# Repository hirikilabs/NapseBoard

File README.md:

# NapseBoard

KiCAD design files for the Napse EEG Board.

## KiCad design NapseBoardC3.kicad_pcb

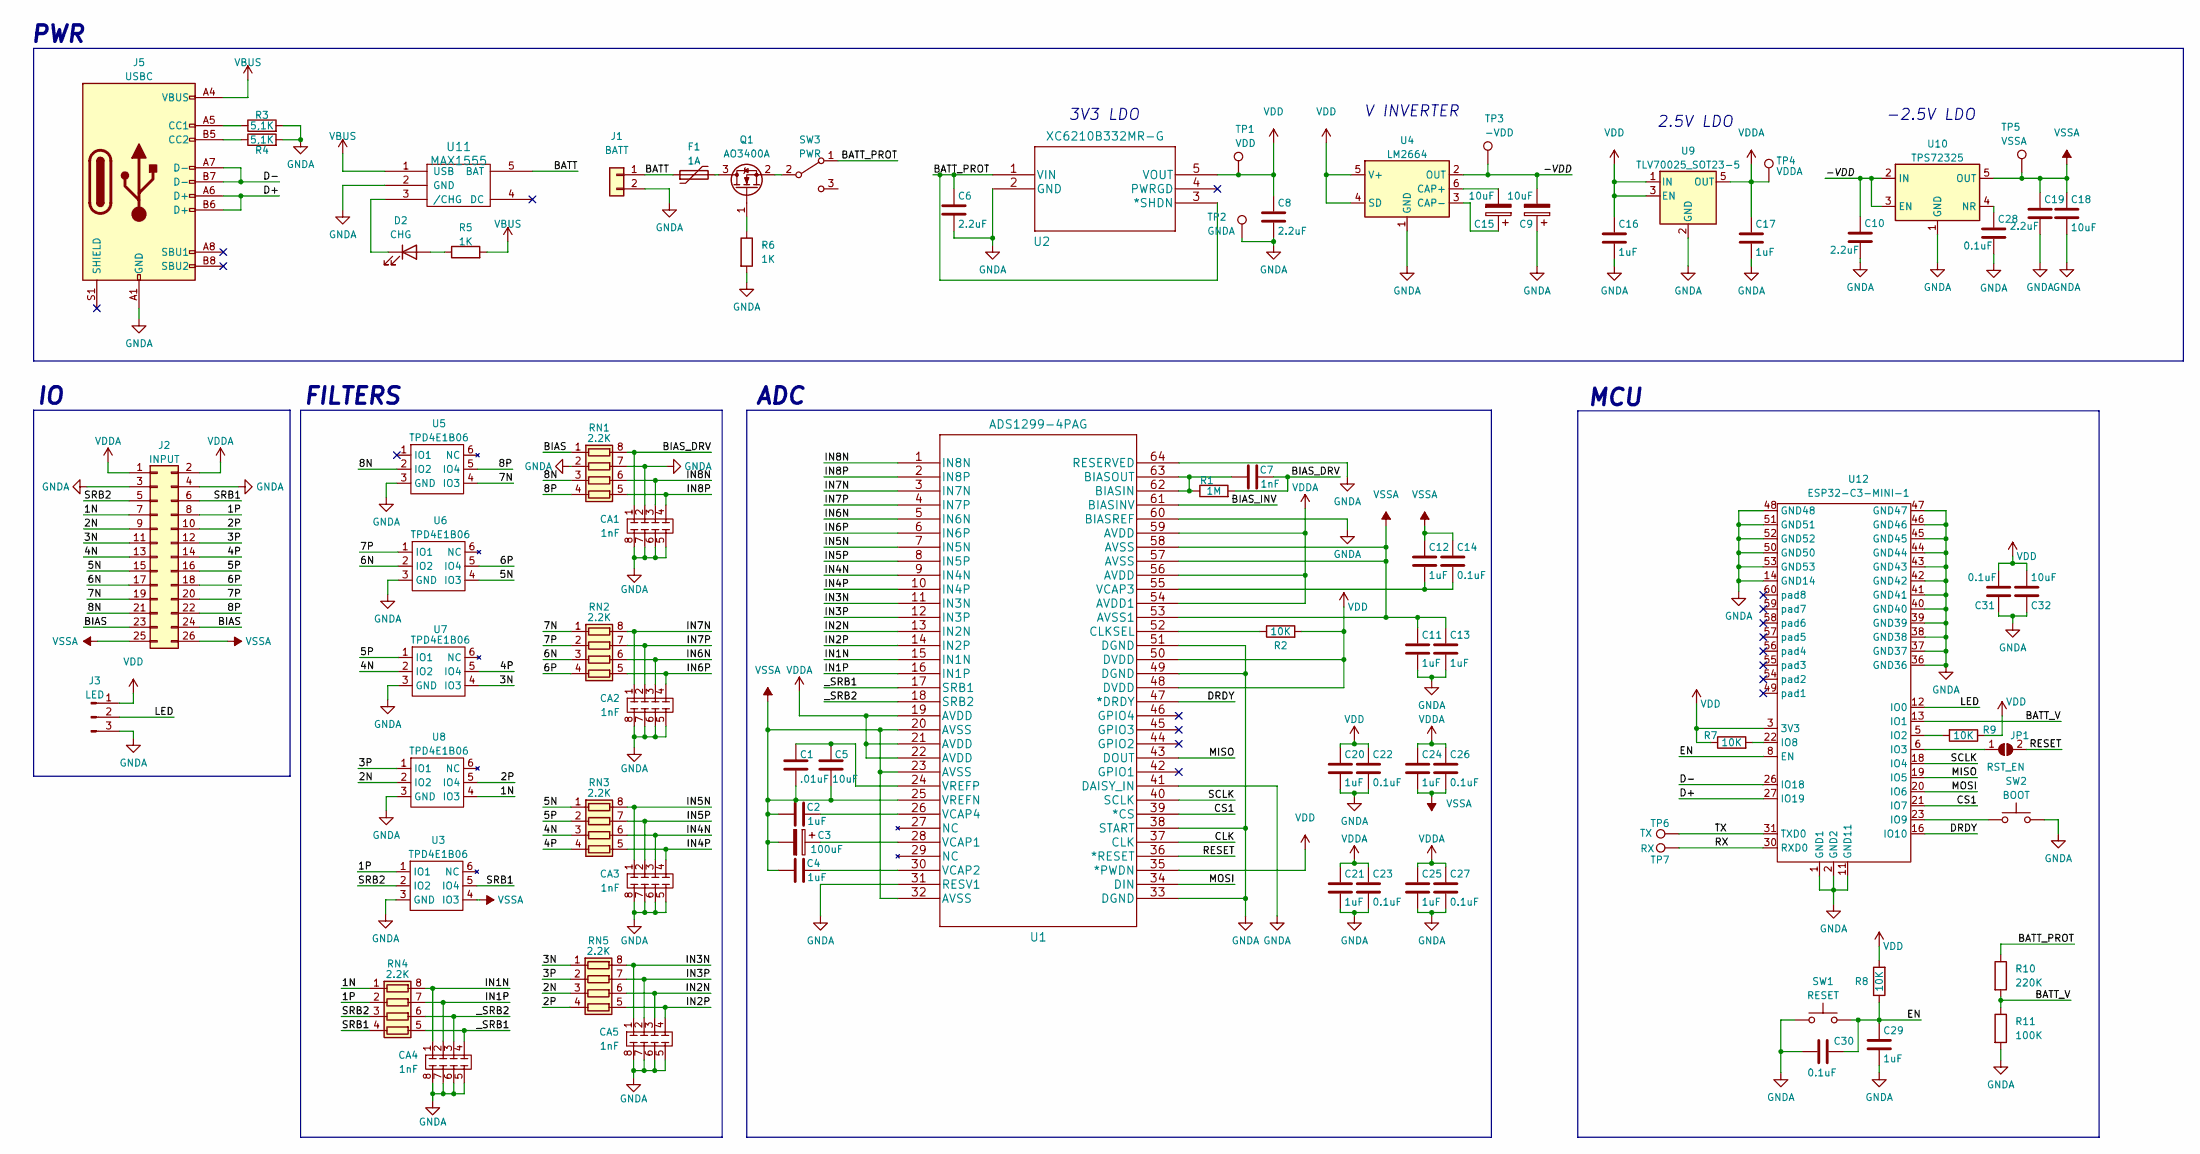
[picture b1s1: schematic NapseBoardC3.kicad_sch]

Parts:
C1: .01uF; C_0603_1608Metric
C2, C4, C11, C12, C13, C16, C17, C20, C21, C24, C25, C29: 1uF; C_0603_1608Metric
C3: 100uF; CP_EIA-3216-18_Kemet-A
C5, C9, C15, C18, C32: 10uF; C_0603_1608Metric
C6, C8, C10, C19: 2.2uF; C_0603_1608Metric
C7: 1nF; C_0603_1608Metric
C14, C22, C23, C26, C27, C28, C30, C31: 0.1uF; C_0603_1608Metric
CA1, CA2, CA3, CA4, CA5: 1nF; C_Array_4x0612
D2: CHG; LED_0603_1608Metric
F1: 1A; Fuse_1206_3216Metric
J1: BATT; PinHeader_1x02_P2.54mm_Vertical
J2: INPUT; PinHeader_2x13_P2.54mm_Horizontal
J3: LED; PinSocket_1x03_P2.00mm_Vertical
J5: USBC; USB_C_Receptacle_XKB_U262-16XN-4BVC11
JP1: RST_EN; SolderJumper-2_P1.3mm_Open_TrianglePad1.0x1.5mm
Q1: AO3400A; SOT-23
R1: 1M; R_0603_1608Metric
R2, R7, R8, R9: 10K; R_0603_1608Metric
R3, R4: 5,1K; R_0603_1608Metric
R5, R6: 1K; R_0603_1608Metric
R10: 220K; R_0603_1608Metric
R11: 100K; R_0603_1608Metric
RN1, RN2, RN3, RN4, RN5: 2.2K; R_Array_Convex_4x0603
SW1: RESET; SW_Push_SPST_NO_Alps_SKRK
SW2: BOOT; SW_Push_SPST_NO_Alps_SKRK
SW3: PWR; SW_SPDT_PCM12
TP1: VDD; TestPoint_Pad_D1.0mm
TP2: GNDA; TestPoint_Pad_D1.0mm
TP3: -VDD; TestPoint_Pad_D1.0mm
TP4: VDDA; TestPoint_Pad_D1.0mm
TP5: VSSA; TestPoint_Pad_D1.0mm
TP6: TX; TestPoint_Pad_D1.0mm
TP7: RX; TestPoint_Pad_D1.0mm
U1: ADS1299-4PAG; TQFP-64_10x10mm_P0.5mm
U2: XC6210B332MR-G; SOT-23-5
U3, U5, U6, U7, U8: TPD4E1B06; SOT-363_SC-70-6
U4: LM2664; SOT-23-6
U9: TLV70025_SOT23-5; SOT-23-5
U10: TPS72325; SOT-23-5
U11: MAX1555; SOT-23-5
U12: ESP32-C3-MINI-1

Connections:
/1N: J2.7, RN4.1 (R1.1), U8.4 (IO3)
/1P: J2.8, RN4.2 (R2.1), U3.1 (IO1)
/2N: J2.9, RN5.3 (R3.1), U8.2 (IO2)
/2P: J2.10, RN5.4 (R4.1), U8.5 (IO4)
/3N: J2.11, RN5.1 (R1.1), U7.4 (IO3)
/3P: J2.12, RN5.2 (R2.1), U8.1 (IO1)
/4N: J2.13, RN3.3 (R3.1), U7.2 (IO2)
/4P: J2.14, RN3.4 (R4.1), U7.5 (IO4)
/5N: J2.15, RN3.1 (R1.1), U6.4 (IO3)
/5P: J2.16, RN3.2 (R2.1), U7.1 (IO1)
/6N: J2.17, RN2.3 (R3.1), U6.2 (IO2)
/6P: J2.18, RN2.4 (R4.1), U6.5 (IO4)
/7N: J2.19, RN2.1 (R1.1), U5.4 (IO3)
/7P: J2.20, RN2.2 (R2.1), U6.1 (IO1)
/8N: J2.21, RN1.3 (R3.1), U5.2 (IO2)
/8P: J2.22, RN1.4 (R4.1), U5.5 (IO4)
/-VDD: C9.2, C10.1, TP3.1, U4.2 (OUT), U10.2 (IN), U10.3 (EN)
/BATT: F1.1, J1.1, U11.5 (BAT)
/BATT_PROT: C6.1, R10.1, SW3.1 (A), U2.1 (VIN), U2.3 (*SHDN)
/BATT_V: R10.2, R11.1, U12.13 (IO1)
/BIAS: J2.23, J2.24, RN1.1 (R1.1)
/BIAS_DRV: C7.2, CA1.1, R1.2, RN1.8 (R1.2)
/BIAS_INV: U1.61 (BIASINV)
/CLK: U1.37 (CLK)
/CS1: U1.39 (*CS), U12.21 (IO7)
/D+: J5.A6 (D+), J5.B6 (D+), U12.27 (IO19)
/D-: J5.A7 (D-), J5.B7 (D-), U12.26 (IO18)
/DRDY: U1.47 (*DRDY), U12.16 (IO10)
/EN: C29.1, C30.2, R8.1, SW1.2, U12.8 (EN)
/IN1N: CA4.1, RN4.8 (R1.2), U1.15 (IN1N)
/IN1P: CA4.2, RN4.7 (R2.2), U1.16 (IN1P)
/IN2N: CA5.3, RN5.6 (R3.2), U1.13 (IN2N)
/IN2P: CA5.4, RN5.5 (R4.2), U1.14 (IN2P)
/IN3N: CA5.1, RN5.8 (R1.2), U1.11 (IN3N)
/IN3P: CA5.2, RN5.7 (R2.2), U1.12 (IN3P)
/IN4N: CA3.3, RN3.6 (R3.2), U1.9 (IN4N)
/IN4P: CA3.4, RN3.5 (R4.2), U1.10 (IN4P)
/IN5N: CA3.1, RN3.8 (R1.2), U1.7 (IN5N)
/IN5P: CA3.2, RN3.7 (R2.2), U1.8 (IN5P)
/IN6N: CA2.3, RN2.6 (R3.2), U1.5 (IN6N)
/IN6P: CA2.4, RN2.5 (R4.2), U1.6 (IN6P)
/IN7N: CA2.1, RN2.8 (R1.2), U1.3 (IN7N)
/IN7P: CA2.2, RN2.7 (R2.2), U1.4 (IN7P)
/IN8N: CA1.3, RN1.6 (R3.2), U1.1 (IN8N)
/IN8P: CA1.4, RN1.5 (R4.2), U1.2 (IN8P)
/LED: J3.2, U12.12 (IO0)
/MISO: U1.43 (DOUT), U12.19 (IO5)
/MOSI: U1.34 (DIN), U12.20 (IO6)
/RESET: JP1.2 (B), U1.36 (*RESET)
/RX: TP7.1, U12.30 (RXD0)
/SCLK: U1.40 (SCLK), U12.18 (IO4)
/SRB1: J2.6, RN4.4 (R4.1), U3.5 (IO4)
/SRB2: J2.5, RN4.3 (R3.1), U3.2 (IO2)
/TX: TP6.1, U12.31 (TXD0)
/_SRB1: CA4.4, RN4.5 (R4.2), U1.17 (SRB1)
/_SRB2: CA4.3, RN4.6 (R3.2), U1.18 (SRB2)
GNDA: C6.2, C8.2, C9.1, C10.2, C11.2, C13.2, C16.2, C17.2, C18.2, C19.2, C20.2, C21.2, C22.2, C23.2, C25.2, C27.2, C28.2, C29.2, C30.1, C31.2, C32.2, CA1.2, CA1.5, CA1.6, CA1.7, CA1.8, CA2.5, CA2.6, CA2.7, CA2.8, CA3.5, CA3.6, CA3.7, CA3.8, CA4.5, CA4.6, CA4.7, CA4.8, CA5.5, CA5.6, CA5.7, CA5.8, J1.2, J2.3, J2.4, J3.3, J5.A1 (GND), J5.A12 (GND), J5.B1 (GND), J5.B12 (GND), R3.2, R4.2, R6.2, R11.2, RN1.2 (R2.1), RN1.7 (R2.2), SW1.1, SW2.2, TP2.1, U1.31 (RESV1), U1.33 (DGND), U1.38 (START), U1.41 (DAISY_IN), U1.49 (DGND), U1.51 (DGND), U1.60 (BIASREF), U1.64 (RESERVED), U2.2 (GND), U3.3 (GND), U4.1 (GND), U5.3 (GND), U6.3 (GND), U7.3 (GND), U8.3 (GND), U9.2 (GND), U10.1 (GND), U11.2 (GND), U12.1 (GND1), U12.2 (GND2), U12.11 (GND11), U12.14 (GND14), U12.36 (GND36), U12.37 (GND37), U12.38 (GND38), U12.39 (GND39), U12.40 (GND40), U12.41 (GND41), U12.42 (GND42), U12.43 (GND43), U12.44 (GND44), U12.45 (GND45), U12.46 (GND46), U12.47 (GND47), U12.48 (GND48), U12.50 (GND50), U12.51 (GND51), U12.52 (GND52), U12.53 (GND53)
unnamed: D2.2 (A), R5.1
unnamed: D2.1 (K), U11.3 (/CHG)
unnamed: J5.A5 (CC1), R3.1
unnamed: J5.B5 (CC2), R4.1
unnamed: JP1.1 (A), U12.6 (IO3)
unnamed: F1.2, Q1.3 (D)
unnamed: Q1.1 (G), R6.1
unnamed: Q1.2 (S), SW3.2 (B)
unnamed: C7.1, R1.1, U1.62 (BIASIN), U1.63 (BIASOUT)
unnamed: R2.1, U1.52 (CLKSEL)
unnamed: C3.1, U1.28 (VCAP1)
unnamed: C4.2, U1.30 (VCAP2)
unnamed: C12.2, C14.2, U1.55 (VCAP3)
unnamed: C2.2, U1.26 (VCAP4)
unnamed: C1.1, C5.2, U1.24 (VREFP)
unnamed: C15.2, U4.6 (CAP+)
unnamed: C15.1, U4.3 (CAP-)
unnamed: C28.1, U10.4 (NR)
unnamed: R9.2, U12.5 (IO2)
unnamed: R7.2, U12.22 (IO8)
unnamed: SW2.1, U12.23 (IO9)
VBUS: J5.A4 (VBUS), J5.A9 (VBUS), J5.B4 (VBUS), J5.B9 (VBUS), R5.2, U11.1 (USB)
VDD: C8.1, C16.1, C20.1, C22.1, C31.1, C32.1, J3.1, R2.2, R7.1, R8.2, R9.1, TP1.1, U1.35 (*PWDN), U1.48 (DVDD), U1.50 (DVDD), U2.5 (VOUT), U4.4 (SD), U4.5 (V+), U9.1 (IN), U9.3 (EN), U12.3 (3V3)
VDDA: C17.1, C21.1, C23.1, C24.1, C25.1, C26.1, C27.1, J2.1, J2.2, TP4.1, U1.19 (AVDD), U1.21 (AVDD), U1.22 (AVDD), U1.54 (AVDD1), U1.56 (AVDD), U1.59 (AVDD), U9.5 (OUT)
VSSA: C1.2, C2.1, C3.2, C4.1, C5.1, C11.1, C12.1, C13.1, C14.1, C18.1, C19.1, C24.2, C26.2, J2.25, J2.26, TP5.1, U1.20 (AVSS), U1.23 (AVSS), U1.25 (VREFN), U1.32 (AVSS), U1.53 (AVSS1), U1.57 (AVSS), U1.58 (AVSS), U3.4 (IO3), U10.5 (OUT)

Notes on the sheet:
2.5V LDO
V INVERTER
3V3 LDO
FILTERS
MCU
-2.5V LDO
PWR
ADC

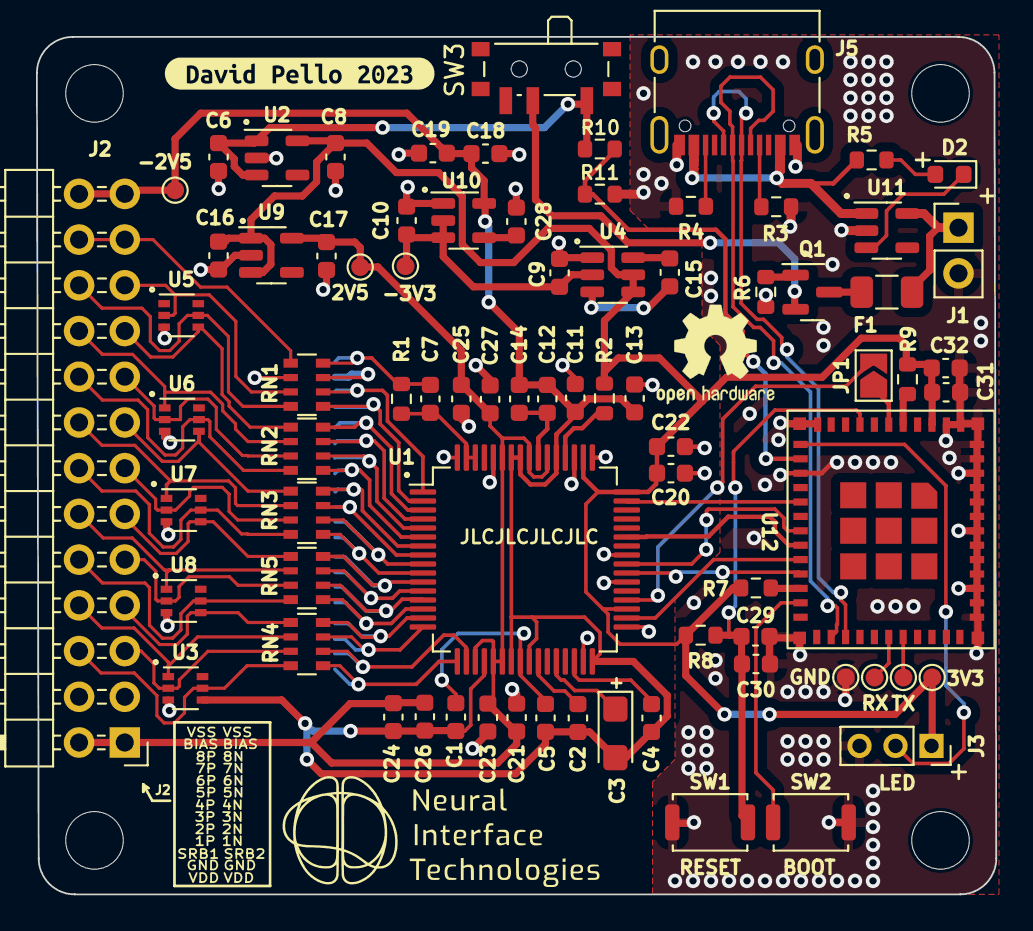
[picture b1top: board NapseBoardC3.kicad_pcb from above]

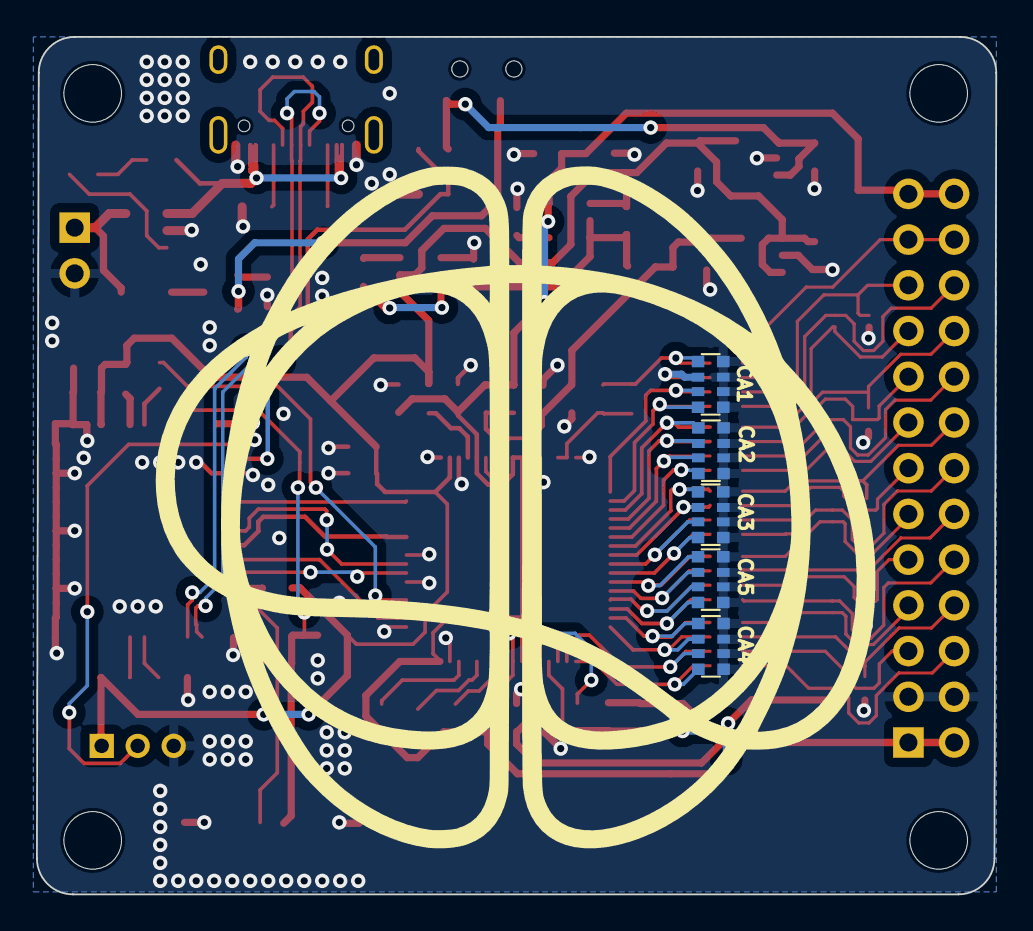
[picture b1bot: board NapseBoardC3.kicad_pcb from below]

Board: 2 copper layers, 53.3 x 47.6 mm, 84 parts (5 on the bottom side), 80 nets.

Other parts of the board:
kibuzzard-645A0FAB: G***; kibuzzard-645A0FAB

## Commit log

2023-09-06 Initial Import
2023-09-06 Added board image
2023-09-06 Added image to readme
